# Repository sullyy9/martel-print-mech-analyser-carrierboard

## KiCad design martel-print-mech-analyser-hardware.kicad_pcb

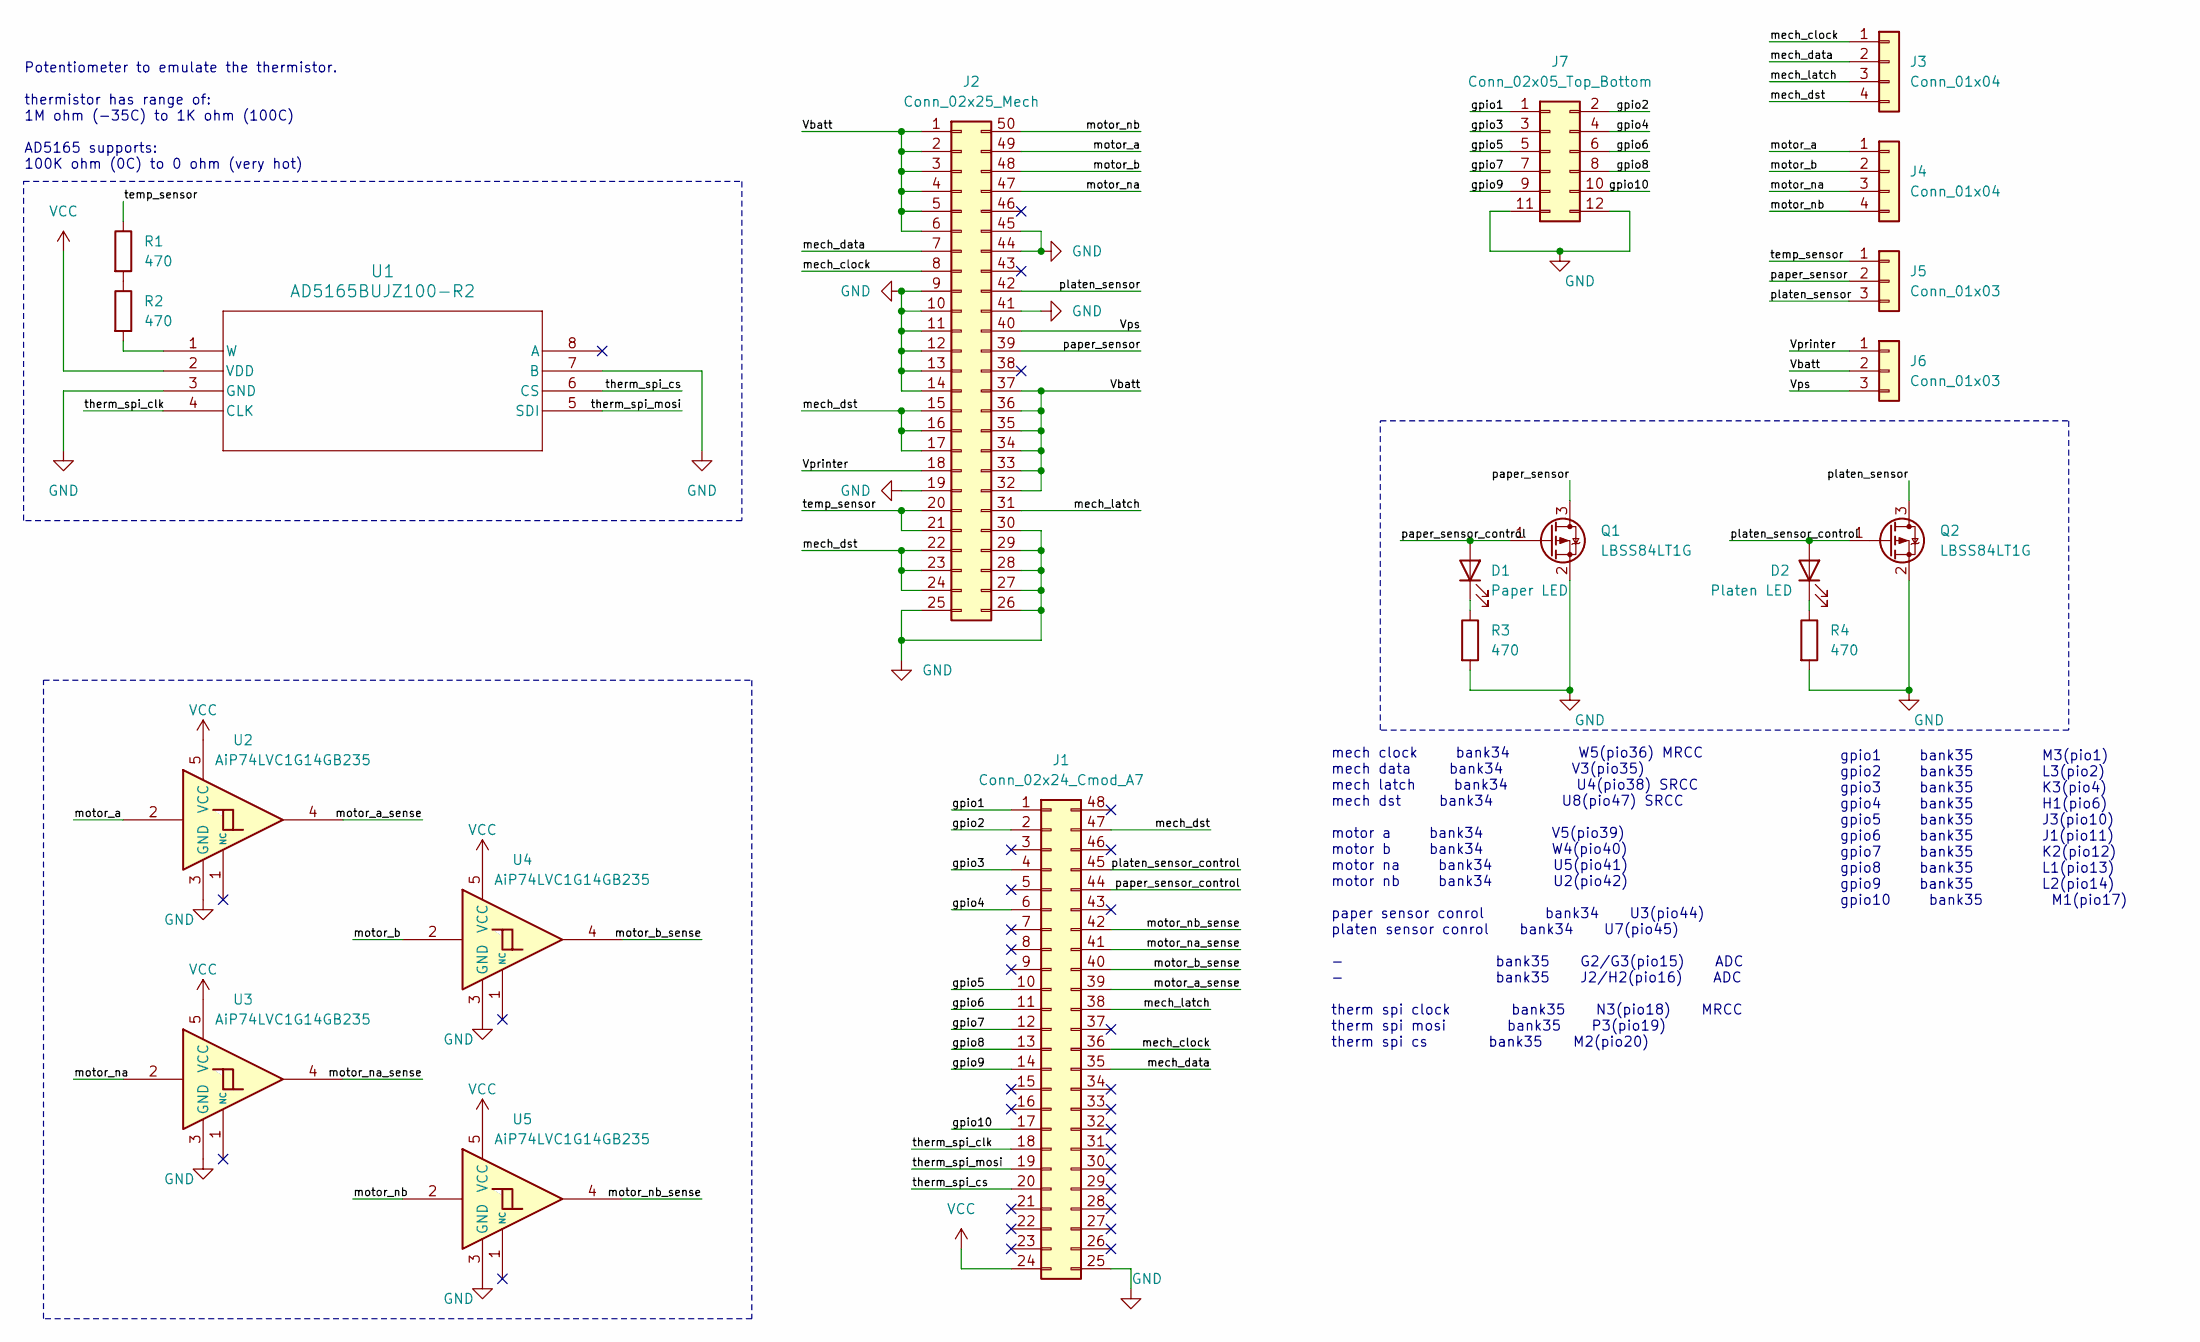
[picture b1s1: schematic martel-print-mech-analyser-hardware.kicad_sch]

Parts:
D1: Paper LED; LED_0805_2012Metric; LCSC Part # C2296
D2: Platen LED; LED_0805_2012Metric; LCSC Part # C2296
J1: Conn_02x24_Cmod_A7; DIP-48_W15.24mm_Socket_LongPads
J2: Conn_02x25_Mech; FH28-50S-0.5SH05_HIR; LCSC Part # C424678
J3, J4: Conn_01x04; PinHeader_1x04_P2.54mm_Vertical; LCSC Part # C2829888
J5, J6: Conn_01x03; PinHeader_1x03_P2.54mm_Vertical; LCSC Part # C2685130
J7: Conn_02x05_Top_Bottom; PinHeader_2x06_P2.54mm_Vertical; LCSC Part # C492423
Q1, Q2: LBSS84LT1G; SOT-23; LCSC Part # C8492
R1, R2, R3, R4: 470; R_0402_1005Metric; LCSC Part # C25117
U1: AD5165BUJZ100-R2; UJ_8_ADI; LCSC Part # C578144
U2, U3, U4, U5: AiP74LVC1G14GB235; SOT-23-5; LCSC Part # C3294715

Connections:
/Vbatt: J2.1, J2.2, J2.3, J2.4, J2.5, J2.6, J2.32, J2.33, J2.34, J2.35, J2.36, J2.37, J6.2
/Vprinter: J2.18, J6.1
/Vps: J2.40, J6.3
/gpio1: J1.1, J7.1
/gpio2: J1.2, J7.2
/gpio3: J1.4, J7.3
/gpio4: J1.6, J7.4
/gpio5: J1.10, J7.5
/gpio6: J1.11, J7.6
/gpio7: J1.12, J7.7
/gpio8: J1.13, J7.8
/gpio9: J1.14, J7.9
/gpio10: J1.17, J7.10
/mech_clock: J1.36, J2.8, J3.1
/mech_data: J1.35, J2.7, J3.2
/mech_dst: J1.47, J2.15, J2.16, J2.17, J2.22, J2.23, J2.24, J3.4
/mech_latch: J1.38, J2.31, J3.3
/motor_a: J2.49, J4.1, U2.2
/motor_a_sense: J1.39, U2.4
/motor_b: J2.48, J4.2, U4.2
/motor_b_sense: J1.40, U4.4
/motor_na: J2.47, J4.3, U3.2
/motor_na_sense: J1.41, U3.4
/motor_nb: J2.50, J4.4, U5.2
/motor_nb_sense: J1.42, U5.4
/paper_sensor: J2.39, J5.2, Q1.3 (D)
/paper_sensor_control: D1.2 (A), J1.44, Q1.1 (G)
/platen_sensor: J2.42, J5.3, Q2.3 (D)
/platen_sensor_control: D2.2 (A), J1.45, Q2.1 (G)
/temp_sensor: J2.20, J2.21, J5.1, R1.1
/therm_spi_clk: J1.18, U1.4 (CLK)
/therm_spi_cs: J1.20, U1.6 (CS)
/therm_spi_mosi: J1.19, U1.5 (SDI)
GND: J1.25, J2.9, J2.10, J2.11, J2.12, J2.13, J2.14, J2.19, J2.25, J2.26, J2.27, J2.28, J2.29, J2.30, J2.41, J2.44, J2.45, J7.11, J7.12, Q1.2 (S), Q2.2 (S), R3.2, R4.2, U1.3 (GND), U1.7 (B), U2.3 (GND), U3.3 (GND), U4.3 (GND), U5.3 (GND)
unnamed: D1.1 (K), R3.1
unnamed: D2.1 (K), R4.1
unnamed: R1.2, R2.1
unnamed: R2.2, U1.1 (W)
VCC: J1.24, U1.2 (VDD), U2.5 (VCC), U3.5 (VCC), U4.5 (VCC), U5.5 (VCC)

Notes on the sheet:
mech clock bank34 W5(pio36) MRCC mech data bank34 V3(pio35) mech latch bank34 U4(pio38) SRCC mech dst bank34 U8(pio47) SRCC motor a bank34 V5(pio39) motor b bank34 W4(pio40) motor na bank34 U5(pio41) motor nb bank34 U2(pio42) paper sensor conrol bank34 U3(pio44) platen sensor conrol bank34 U7(pio45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
Potentiometer to emulate the thermistor. thermistor has range of: 1M ohm (-35C) to 1K ohm (100C) AD5165 supports: 100K ohm (0C) to 0 ohm (very hot)
gpio1 bank35 M3(pio1) gpio2 bank35 L3(pio2) gpio3 bank35 K3(pio4) gpio4 bank35 H1(pio6) gpio5 bank35 J3(pio10) gpio6 bank35 J1(pio11) gpio7 bank35 K2(pio12) gpio8 bank35 L1(pio13) gpio9 bank35 L2(pio14) gpio10 bank35 M1(pio17)

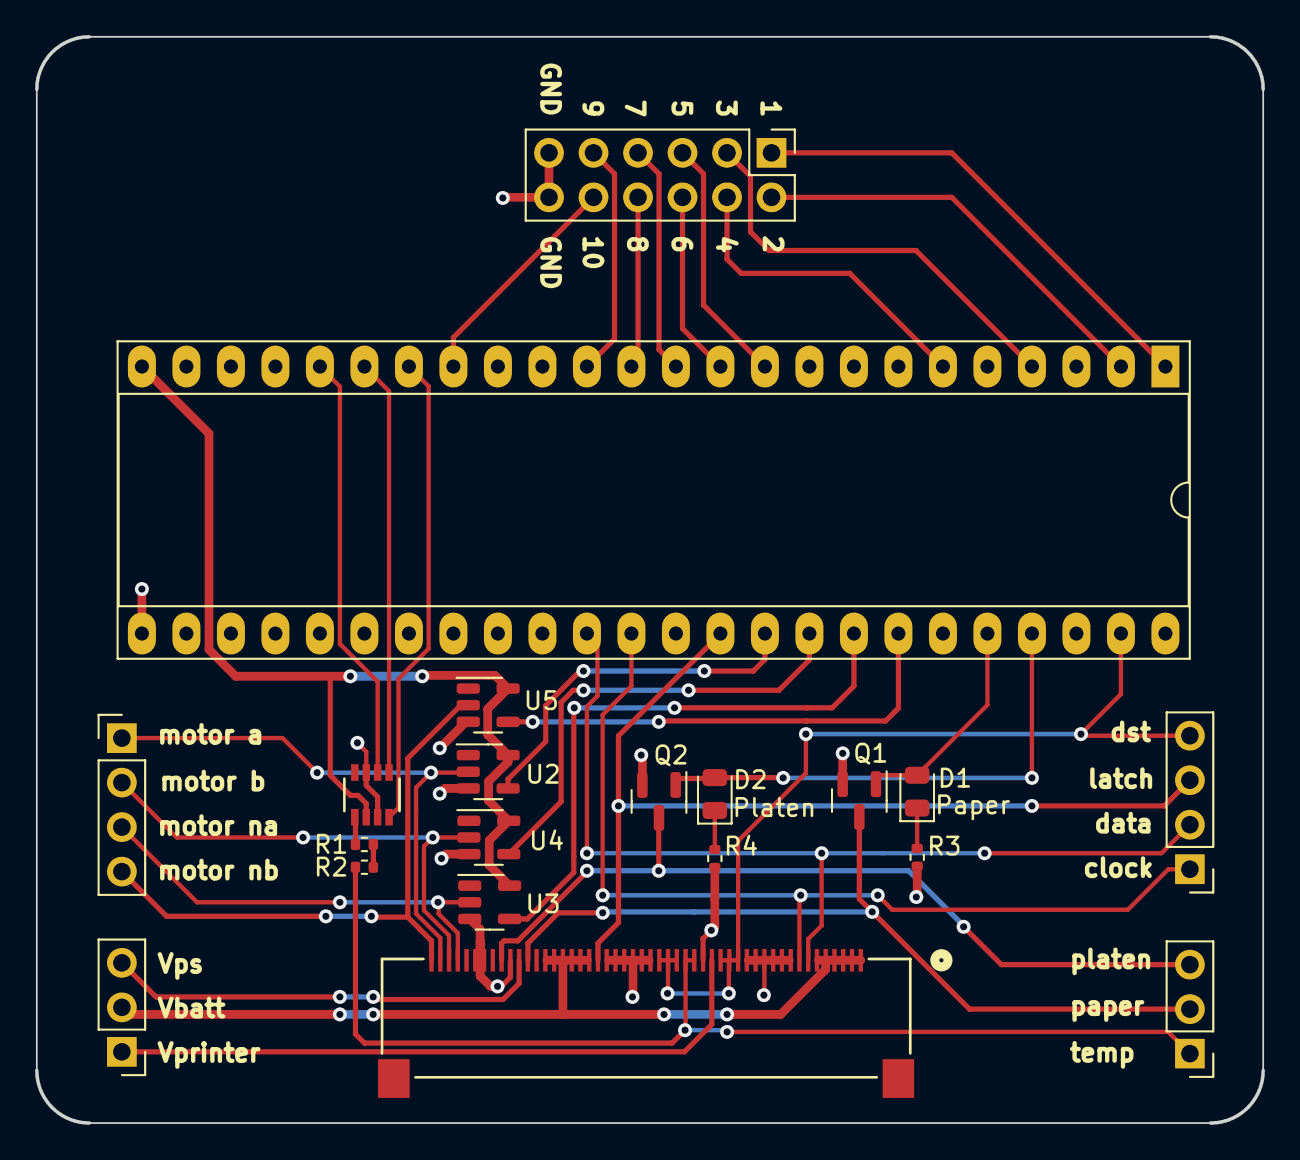
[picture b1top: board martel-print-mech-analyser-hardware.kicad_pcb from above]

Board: 2 copper layers, 70.0 x 62.0 mm, 20 parts (0 on the bottom side), 39 nets.
